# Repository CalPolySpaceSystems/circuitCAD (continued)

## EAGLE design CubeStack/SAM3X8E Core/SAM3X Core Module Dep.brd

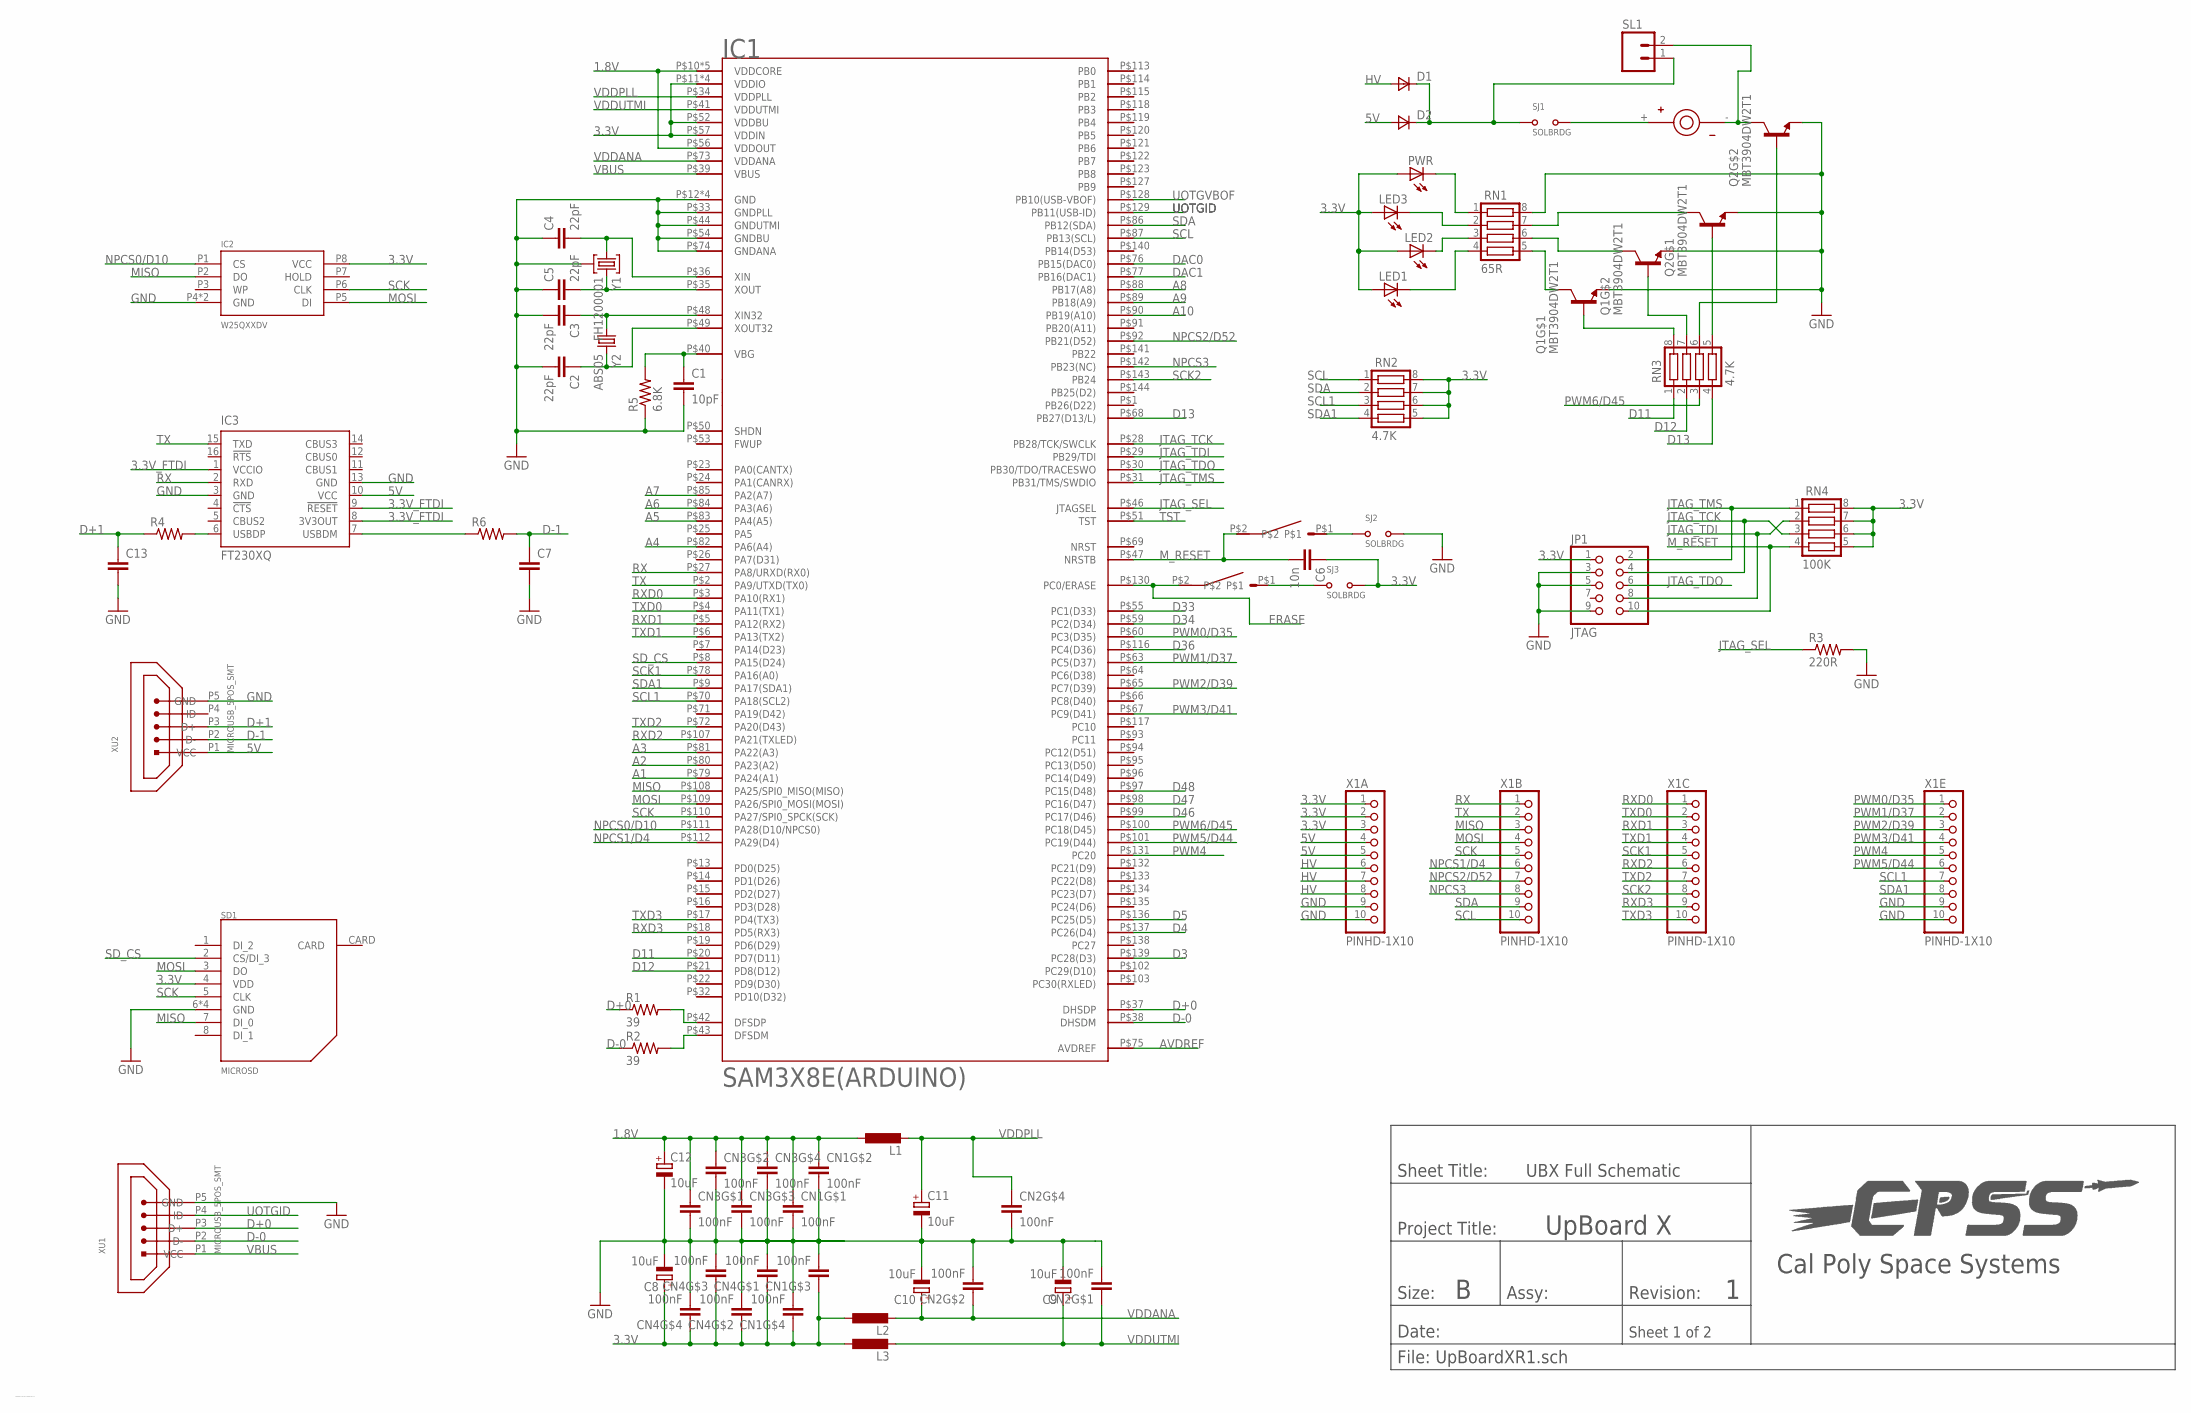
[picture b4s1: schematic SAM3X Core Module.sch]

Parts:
C1: 10pF; C0603
C2, C3, C4, C5: 22pF; C0603
C6: 10n; C0603
C7, C13: C-EUC0603; C0603
C8, C9, C10, C11, C12: 10uF; A/3216-18R
CN1, CN2, CN3, CN4: 100nF; 1206-4
D1, D2: DSOD323; SOD323
ERASE: 1000P; B3U-1000P
IC1: SAM3X8E(ARDUINO); 144-LEAD_LQFP
IC2: W25QXXDV; WSON
IC3: FT230XQ; QFN16
JP1: JTAG; 2X5-PTH-1.27MM
L1, L2, L3: L-EU0402; C0402
LED1, LED2, LED3: LEDCHIPLED_0805; CHIPLED_0805
LS1: AI-1440-TWT-24V-2-R; AI-1440-TWT-24-2-R
PWR: LEDCHIPLED_0805; CHIPLED_0805
Q1, Q2: MBT3904DW2T1; SOT-363
R1, R2: 39; R0603
R3: 220R; R0402
R4, R6: R-US_R0603; R0603
R5: 6.8K; R0603
RESET: 1000P; B3U-1000P
RN1: 65R; CTS742C083
RN2, RN3: 4.7K; CTS742C083
RN4: 100K; CTS742C083
SD1: MICROSD; CONN_MICROSD
SJ1, SJ2, SJ3: SOLBRDG
SL1: M02; 02P
X1A, X1B, X1C, X1E: PINHD-1X10; 1X10-BIG
XU1, XU2: MICROUSB_5POS_SMT; RECPT_SMT_R/A
Y1: FH1200001; MINISMD
Y2: ABS05; FC-12M

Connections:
1.8V: C12.+, CN1.P$1 (1), CN1.P$2 (1), CN3.P$1 (1), CN3.P$2 (1), CN3.P$3 (1), CN3.P$4 (1), IC1.P$10 (VDDCORE), IC1.P$45 (VDDCORE), IC1.P$56 (VDDOUT), IC1.P$61 (VDDCORE), IC1.P$104 (VDDCORE), IC1.P$124 (VDDCORE), L1.1
3.3V: C6.1, C8.+, CN1.P$3 (1), CN1.P$4 (1), CN4.P$1 (1), CN4.P$2 (1), CN4.P$3 (1), CN4.P$4 (1), IC1.P$11 (VDDIO), IC1.P$52 (VDDBU), IC1.P$57 (VDDIN), IC1.P$62 (VDDIO), IC1.P$105 (VDDIO), IC1.P$125 (VDDIO), IC2.P8 (VCC), JP1.1, L2.1, L3.1, LED1.A, LED2.A, LED3.A, PWR.A, RN2.5, RN2.6, RN2.7, RN2.8, RN4.5, RN4.6, RN4.7, RN4.8, SD1.4 (VDD), SJ3.P$2, X1A.1, X1A.2, X1A.3; also elsewhere on the board
3.3V_FTDI: IC3.1 (VCCIO), IC3.8 (3V3OUT), IC3.9 (!RESET)
5V: D2.2 (A), IC3.10 (VCC), X1A.4, X1A.5, XU2.P1 (VCC)
A1: IC1.P$79 (PA24(A1))
A2: IC1.P$80 (PA23(A2))
A3: IC1.P$81 (PA22(A3))
A4: IC1.P$82 (PA6(A4))
A5: IC1.P$83 (PA4(A5))
A6: IC1.P$84 (PA3(A6))
A7: IC1.P$85 (PA2(A7))
A8: IC1.P$88 (PB17(A8))
A9: IC1.P$89 (PB18(A9))
A10: IC1.P$90 (PB19(A10))
AVDREF: IC1.P$75 (AVDREF)
D3: IC1.P$139 (PC28(D3))
D4: IC1.P$137 (PC26(D4))
D5: IC1.P$136 (PC25(D5))
D11: IC1.P$20 (PD7(D11)), RN3.1
D12: IC1.P$21 (PD8(D12)), RN3.2
D13: IC1.P$68 (PB27(D13/L)), RN3.4
D33: IC1.P$55 (PC1(D33))
D34: IC1.P$59 (PC2(D34))
D36: IC1.P$116 (PC4(D36))
D46: IC1.P$99 (PC17(D46))
D47: IC1.P$98 (PC16(D47))
D48: IC1.P$97 (PC15(D48))
D+0: IC1.P$37 (DHSDP), R1.1, XU1.P3 (D+)
D+1: C13.1, R4.1, XU2.P3 (D+)
D-0: IC1.P$38 (DHSDM), R2.1, XU1.P2 (D-)
D-1: C7.1, R6.2, XU2.P2 (D-)
DAC0: IC1.P$76 (PB15(DAC0))
DAC1: IC1.P$77 (PB16(DAC1))
ERASE: ERASE.P$2, IC1.P$130 (PC0/ERASE)
GND: C1.2, C2.2, C3.2, C4.1, C5.1, C7.2, C8.-, C9.-, C10.-, C11.-, C12.-, C13.2, CN1.P$5 (2), CN1.P$6 (2), CN1.P$7 (2), CN1.P$8 (2), CN2.P$5 (2), CN2.P$6 (2), CN2.P$8 (2), CN3.P$5 (2), CN3.P$6 (2), CN3.P$7 (2), CN3.P$8 (2), CN4.P$5 (2), CN4.P$6 (2), CN4.P$7 (2), CN4.P$8 (2), IC1.P$12 (GND), IC1.P$33 (GNDPLL), IC1.P$44 (GNDUTMI), IC1.P$54 (GNDBU), IC1.P$58 (GND), IC1.P$74 (GNDANA), IC1.P$106 (GND), IC1.P$126 (GND), IC2.P4 (GND), IC2.TH (GND), IC3.3 (GND), IC3.13 (GND), JP1.3, JP1.5, JP1.9, Q1.P$1 (E), Q1.P$4 (E), Q2.P$1 (E), Q2.P$4 (E), R3.2, R5.1, RN1.8, SD1.6 (GND), SD1.GND1 (GND), SD1.GND2 (GND), SD1.GND3 (GND), SJ2.P$2, X1A.9, X1A.10, X1E.9, X1E.10, XU1.P5 (GND), XU2.P5 (GND), Y1.GND2 (2), Y1.GND4 (2); also elsewhere on the board
HV: D1.2 (A), X1A.6, X1A.7, X1A.8
JTAG_SEL: IC1.P$46 (JTAGSEL), R3.1
JTAG_TCK: IC1.P$28 (PB28/TCK/SWCLK), JP1.4, RN4.3
JTAG_TDI: IC1.P$29 (PB29/TDI), JP1.8, RN4.2
JTAG_TDO: IC1.P$30 (PB30/TDO/TRACESWO), JP1.6
JTAG_TMS: IC1.P$31 (PB31/TMS/SWDIO), JP1.2, RN4.1
LS_D: LS1.-, Q2.P$6 (C), SL1.2
LS_DRIVE: D1.1 (C), D2.1 (C), SJ1.P$1, SL1.1
LS_G: Q2.P$2 (B), RN3.6
L_1: LED1.C, RN1.4
L_1_D: Q1.P$3 (C), RN1.5
L_1_G: Q1.P$5 (B), RN3.8
L_2: LED2.C, RN1.3
L_2_D: Q1.P$6 (C), RN1.6
L_2_G: Q1.P$2 (B), RN3.7
L_3: LED3.C, RN1.2
L_3_D: Q2.P$3 (C), RN1.7
L_3_G: Q2.P$5 (B), RN3.5
L_PWR_D: PWR.C, RN1.1
MISO: IC1.P$108 (PA25/SPI0_MISO(MISO)), IC2.P2 (DO), SD1.7 (DI_0), X1B.3
MOSI: IC1.P$109 (PA26/SPI0_MOSI(MOSI)), IC2.P5 (DI), SD1.3 (DO), X1B.4
M_RESET: C6.2, IC1.P$47 (NRSTB), JP1.10, RESET.P$2, RN4.4
unnamed: LS1.+, SJ1.P$2
unnamed: IC1.P$42 (DFSDP), R1.2
unnamed: IC3.6 (USBDP), R4.2
unnamed: IC3.7 (USBDM), R6.1
unnamed: RESET.P$1, SJ2.P$1
unnamed: IC1.P$43 (DFSDM), R2.2
unnamed: ERASE.P$1, SJ3.P$1
unnamed: C2.1, IC1.P$49 (XOUT32), Y2.2
unnamed: C3.1, IC1.P$48 (XIN32), Y2.1
unnamed: C1.1, IC1.P$40 (VBG), R5.2
NPCS0/D10: IC1.P$111 (PA28(D10/NPCS0)), IC2.P1 (CS); also elsewhere on the board
NPCS1/D4: IC1.P$112 (PA29(D4)), X1B.6
NPCS2/D52: IC1.P$92 (PB21(D52)), X1B.7
NPCS3: IC1.P$142 (PB23(NC)), X1B.8
PWM0/D35: IC1.P$60 (PC3(D35)), X1E.1
PWM1/D37: IC1.P$63 (PC5(D37)), X1E.2
PWM2/D39: IC1.P$65 (PC7(D39)), X1E.3
PWM3/D41: IC1.P$67 (PC9(D41)), X1E.4
PWM4: IC1.P$131 (PC20), X1E.5
PWM5/D44: IC1.P$101 (PC19(D44)), X1E.6
PWM6/D45: IC1.P$100 (PC18(D45)), RN3.3
RX: IC1.P$27 (PA8/URXD(RX0)), IC3.2 (RXD), X1B.1
RXD0: IC1.P$3 (PA10(RX1)), X1C.1
RXD1: IC1.P$5 (PA12(RX2)), X1C.3
RXD2: IC1.P$107 (PA21(TXLED)), X1C.6
RXD3: IC1.P$18 (PD5(RX3)), X1C.9
SCK: IC1.P$110 (PA27/SPI0_SPCK(SCK)), IC2.P6 (CLK), SD1.5 (CLK), X1B.5
SCK1: IC1.P$78 (PA16(A0)), X1C.5
SCK2: IC1.P$143 (PB24), X1C.8
SCL: IC1.P$87 (PB13(SCL)), RN2.1, X1B.10
SCL1: IC1.P$70 (PA18(SCL2)), RN2.3, X1E.7
SDA: IC1.P$86 (PB12(SDA)), RN2.2, X1B.9
SDA1: IC1.P$9 (PA17(SDA1)), RN2.4, X1E.8
SD_CS: IC1.P$8 (PA15(D24)), SD1.2 (CS/DI_3)
TST: IC1.P$51 (TST)
TX: IC1.P$2 (PA9/UTXD(TX0)), IC3.15 (TXD), X1B.2
TXD0: IC1.P$4 (PA11(TX1)), X1C.2
TXD1: IC1.P$6 (PA13(TX2)), X1C.4
TXD2: IC1.P$72 (PA20(D43)), X1C.7
TXD3: IC1.P$17 (PD4(TX3)), X1C.10
UOTGID: IC1.P$129 (PB11(USB-ID)), XU1.P4 (ID)
UOTGVBOF: IC1.P$128 (PB10(USB-VBOF))
VBUS: IC1.P$39 (VBUS), XU1.P1 (VCC)
VDDANA: C10.+, CN2.P$2 (1), IC1.P$73 (VDDANA), L2.2
VDDPLL: C11.+, CN2.P$4 (1), IC1.P$34 (VDDPLL), L1.2
VDDUTMI: C9.+, CN2.P$1 (1), IC1.P$41 (VDDUTMI), L3.2
XCK_N: C5.2, IC1.P$35 (XOUT), Y1.P3 (3)
XCK_P: C4.2, IC1.P$36 (XIN), Y1.P1 (1)

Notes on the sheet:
Assy:
Size:
Revision:
Sheet 1 of 2
Date:
Sheet Title:
Project Title:
File: UpBoardXR1.sch
UBX Full Schematic
UpBoard X
C:/Users/Patrick Chizek/Pictures/CPSSLOGO.bmp
Cal Poly Space Systems

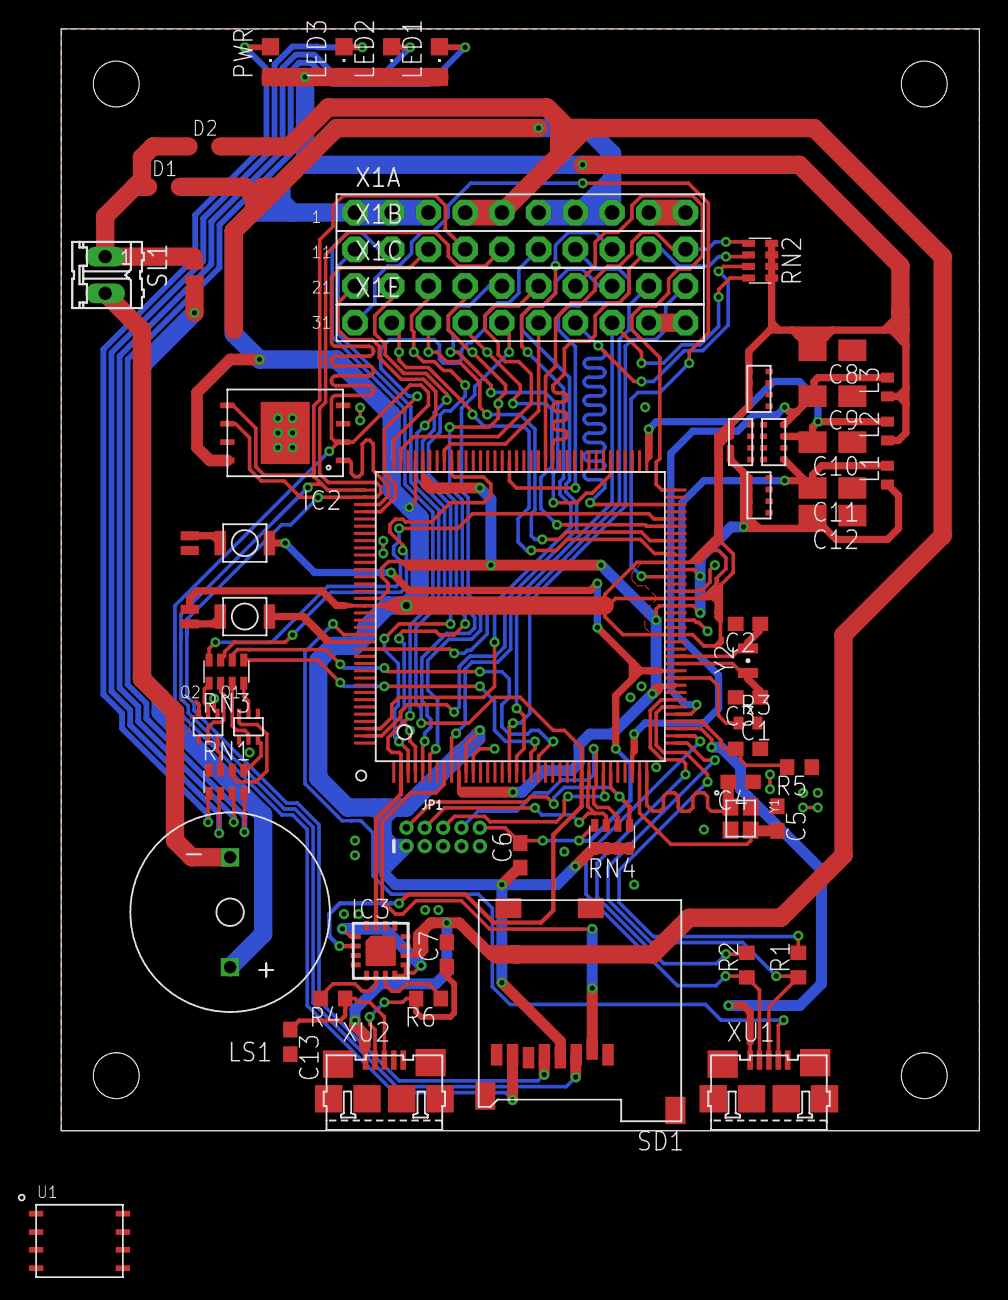
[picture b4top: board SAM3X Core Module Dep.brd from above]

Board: 2 copper layers, 63.5 x 76.2 mm, 59 parts (0 on the bottom side), 81 nets.

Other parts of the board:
U1: SST26VF064B; SOIJ

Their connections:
3.3V: U1.P$8; also elsewhere on the board
GND: U1.P$4; also elsewhere on the board
NPCS0/D10: U1.P$1; also elsewhere on the board

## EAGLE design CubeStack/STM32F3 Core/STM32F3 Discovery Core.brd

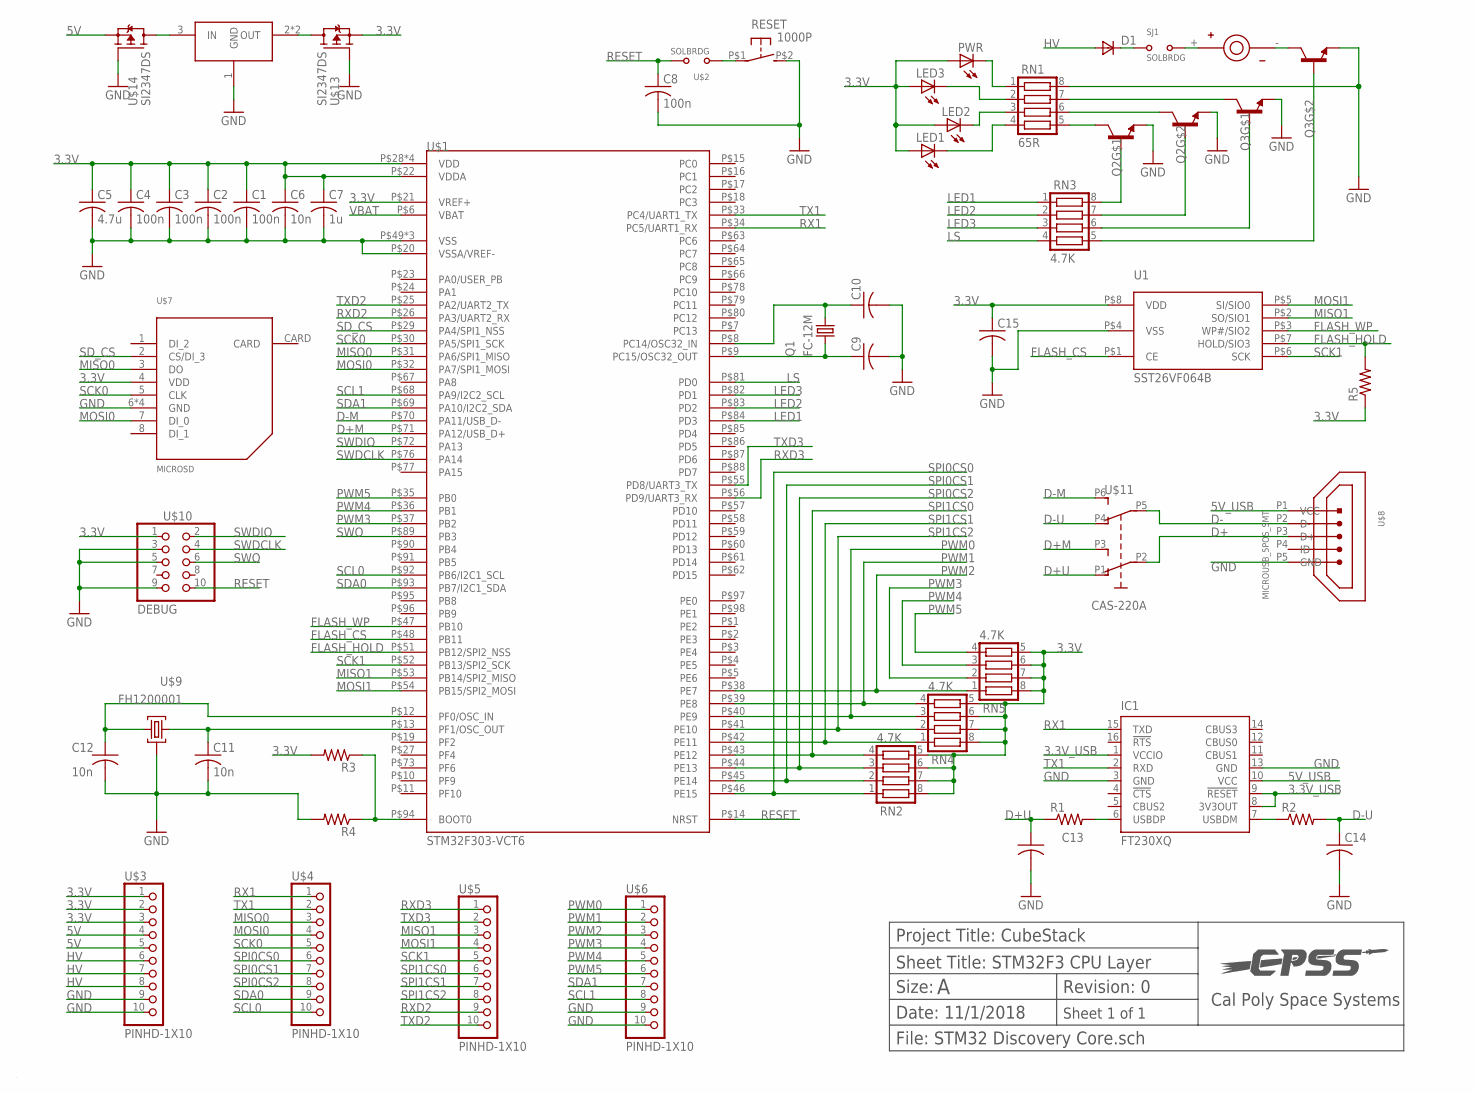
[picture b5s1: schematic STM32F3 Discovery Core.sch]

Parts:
C1, C2, C3, C4: 100n; C0805
C5: 4.7u; C0805
C6: 10n; C0805
C7: 1u; C0805
C8: 100n; C0603
C9, C10, C15: C-USC0402; C0402
C11, C12: 10n; C0402
C13, C14: C-USC0603; C0603
D1: DSOD323; SOD323
IC1: FT230XQ; QFN16
LED1, LED2, LED3: LEDCHIPLED_0805; CHIPLED_0805
LS1: AI-1440-TWT-24V-2-R; AI-1440-TWT-24-2-R
PWR: LEDCHIPLED_0805; CHIPLED_0805
Q1: FC-12M
Q2, Q3: MBT3904DW2T1; SOT-363
R1, R2, R3, R4, R5: R-US_R0603; R0603
RESET: 1000P; B3U-1000P
RN1: 65R; CTS742C083
RN2, RN3, RN4, RN5: 4.7K; CTS742C083
SJ1: SOLBRDG
U1: SST26VF064B; SOIJ
U$1: STM32F303-VCT6; LQFP-100
U$2: SOLBRDG
U$3, U$4, U$5, U$6: PINHD-1X10; 1X10-BIG
U$7: MICROSD; CONN_MICROSD
U$8: MICROUSB_5POS_SMT; RECPT_SMT_R/A
U$9: FH1200001; MINISMD
U$10: DEBUG; 2X5-PTH-1.27MM
U$11: CAS-220A; CAS220B1
U$12: AZ1117C; SOT89
U$13, U$14: SI2347DS; SOT23

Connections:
3.3V: C1.1, C2.1, C3.1, C4.1, C5.1, C6.1, C7.1, C15.1, LED1.A, LED2.A, LED3.A, PWR.A, R3.2, R5.1, RN2.5, RN2.6, RN2.7, RN2.8, RN4.5, RN4.6, RN4.7, RN4.8, RN5.5, RN5.6, RN5.7, RN5.8, U1.P$8 (VDD), U$1.P$21 (VREF+), U$1.P$22 (VDDA), U$1.P$28 (VDD), U$1.P$50 (VDD), U$1.P$75 (VDD), U$1.P$100 (VDD), U$3.1, U$3.2, U$3.3, U$7.4 (VDD), U$10.1, U$13.2 (S)
3.3V_USB: IC1.1 (VCCIO), IC1.8 (3V3OUT), IC1.9 (!RESET), U$12.2 (OUT), U$12.2@1 (OUT), U$13.3 (D)
5V: U$3.4, U$3.5, U$14.2 (S)
5V_USB: IC1.10 (VCC), U$8.P1 (VCC), U$12.3 (IN), U$14.3 (D)
D+: U$8.P3 (D+), U$11.P2
D+M: U$1.P$71 (PA12/USB_D+), U$11.P3 (S)
D+U: C13.1, R1.1, U$11.P1 (O)
D-: U$8.P2 (D-), U$11.P5 (P1)
D-M: U$1.P$70 (PA11/USB_D-), U$11.P6 (S1)
D-U: C14.1, R2.2, U$11.P4 (O1)
FLASH_CS: U1.P$1 (CE), U$1.P$48 (PB11)
FLASH_HOLD: R5.2, U1.P$7 (HOLD/SIO3), U$1.P$51 (PB12/SPI2_NSS)
FLASH_WP: U1.P$3 (WP#/SIO2), U$1.P$47 (PB10)
GND: C1.2, C2.2, C3.2, C4.2, C5.2, C6.2, C7.2, C8.2, C9.2, C10.2, C11.2, C12.2, C13.2, C14.2, C15.2, IC1.3 (GND), IC1.13 (GND), Q2.P$3 (E), Q2.P$6 (E), Q3.P$3 (E), Q3.P$6 (E), R4.2, RESET.P$2 (S), RN1.8, U1.P$4 (VSS), U$1.P$20 (VSSA/VREF-), U$1.P$49 (VSS), U$1.P$74 (VSS), U$1.P$99 (VSS), U$3.9, U$3.10, U$6.9, U$6.10, U$7.6 (GND), U$7.GND1 (GND), U$7.GND2 (GND), U$7.GND3 (GND), U$8.P5 (GND), U$9.GND2 (2), U$9.GND4 (2), U$10.3, U$10.5, U$10.9, U$12.1 (GND), U$13.1 (G), U$14.1 (G)
HV: D1.2 (A), U$3.6, U$3.7, U$3.8
LED1: RN3.1, U$1.P$84 (PD3)
LED2: RN3.2, U$1.P$83 (PD2)
LED3: RN3.3, U$1.P$82 (PD1)
LS: RN3.4, U$1.P$81 (PD0)
LS_D: LS1.-, Q3.P$5 (C)
LS_G: Q3.P$1 (B), RN3.5
L_1: LED1.C, RN1.4
L_1_D: Q2.P$4 (C), RN1.5
L_1_G: Q2.P$2 (B), RN3.8
L_2: LED2.C, RN1.3
L_2_D: Q2.P$5 (C), RN1.6
L_2_G: Q2.P$1 (B), RN3.7
L_3: LED3.C, RN1.2
L_3_D: Q3.P$4 (C), RN1.7
L_3_G: Q3.P$2 (B), RN3.6
L_PWR_D: PWR.C, RN1.1
MISO0: U$1.P$31 (PA6/SPI1_MISO), U$4.3, U$7.3 (DO)
MISO1: U1.P$2 (SO/SIO1), U$1.P$53 (PB14/SPI2_MISO), U$5.3
MOSI0: U$1.P$32 (PA7/SPI1_MOSI), U$4.4, U$7.7 (DI_0)
MOSI1: U1.P$5 (SI/SIO0), U$1.P$54 (PB15/SPI2_MOSI), U$5.4
unnamed: LS1.+, SJ1.P$2
unnamed: C10.1, Q1.2, U$1.P$8 (PC14/OSC32_IN)
unnamed: RESET.P$1, U$2.P$1
unnamed: C9.1, Q1.1, U$1.P$9 (PC15/OSC32_OUT)
unnamed: C12.1, U$1.P$12 (PF0/OSC_IN), U$9.P3 (3)
unnamed: C11.1, U$1.P$13 (PF1/OSC_OUT), U$9.P1 (1)
unnamed: D1.1 (C), SJ1.P$1
unnamed: IC1.6 (USBDP), R1.2
unnamed: IC1.7 (USBDM), R2.1
unnamed: R3.1, R4.1, U$1.P$94 (BOOT0)
PWM0: RN4.3, U$1.P$40 (PE9), U$6.1
PWM1: RN4.4, U$1.P$39 (PE8), U$6.2
PWM2: RN5.1, U$1.P$38 (PE7), U$6.3
PWM3: RN5.2, U$1.P$37 (PB2), U$6.4
PWM4: RN5.3, U$1.P$36 (PB1), U$6.5
PWM5: RN5.4, U$1.P$35 (PB0), U$6.6
RESET: C8.1, U$1.P$14 (NRST), U$2.P$2, U$10.10
RX1: IC1.15 (TXD), U$1.P$34 (PC5/UART1_RX), U$4.1
RXD2: U$1.P$26 (PA3/UART2_RX), U$5.9
RXD3: U$1.P$56 (PD9/UART3_RX), U$5.1
SCK0: U$1.P$30 (PA5/SPI1_SCK), U$4.5, U$7.5 (CLK)
SCK1: U1.P$6 (SCK), U$1.P$52 (PB13/SPI2_SCK), U$5.5
SCL0: U$1.P$92 (PB6/I2C1_SCL), U$4.10
SCL1: U$1.P$68 (PA9/I2C2_SCL), U$6.8
SDA0: U$1.P$93 (PB7/I2C1_SDA), U$4.9
SDA1: U$1.P$69 (PA10/I2C2_SDA), U$6.7
SD_CS: U$1.P$29 (PA4/SPI1_NSS), U$7.2 (CS/DI_3)
SPI0CS0: RN2.1, U$1.P$46 (PE15), U$4.6
SPI0CS1: RN2.2, U$1.P$45 (PE14), U$4.7
SPI0CS2: RN2.3, U$1.P$44 (PE13), U$4.8
SPI1CS0: RN2.4, U$1.P$43 (PE12), U$5.6
SPI1CS1: RN4.1, U$1.P$42 (PE11), U$5.7
SPI1CS2: RN4.2, U$1.P$41 (PE10), U$5.8
SWDCLK: U$1.P$76 (PA14), U$10.4
SWDIO: U$1.P$72 (PA13), U$10.2
SWO: U$1.P$89 (PB3), U$10.6
TX1: IC1.2 (RXD), U$1.P$33 (PC4/UART1_TX), U$4.2
TXD2: U$1.P$25 (PA2/UART2_TX), U$5.10
TXD3: U$1.P$55 (PD8/UART3_TX), U$5.2
VBAT: U$1.P$6 (VBAT)

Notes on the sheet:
Size:
Revision: 0
Sheet 1 of 1
Date: 11/1/2018
Sheet Title: STM32F3 CPU Layer
Project Title: CubeStack
File: STM32 Discovery Core.sch
Cal Poly Space Systems
C:/Users/patri/Pictures/CPSSLOGO.bmp

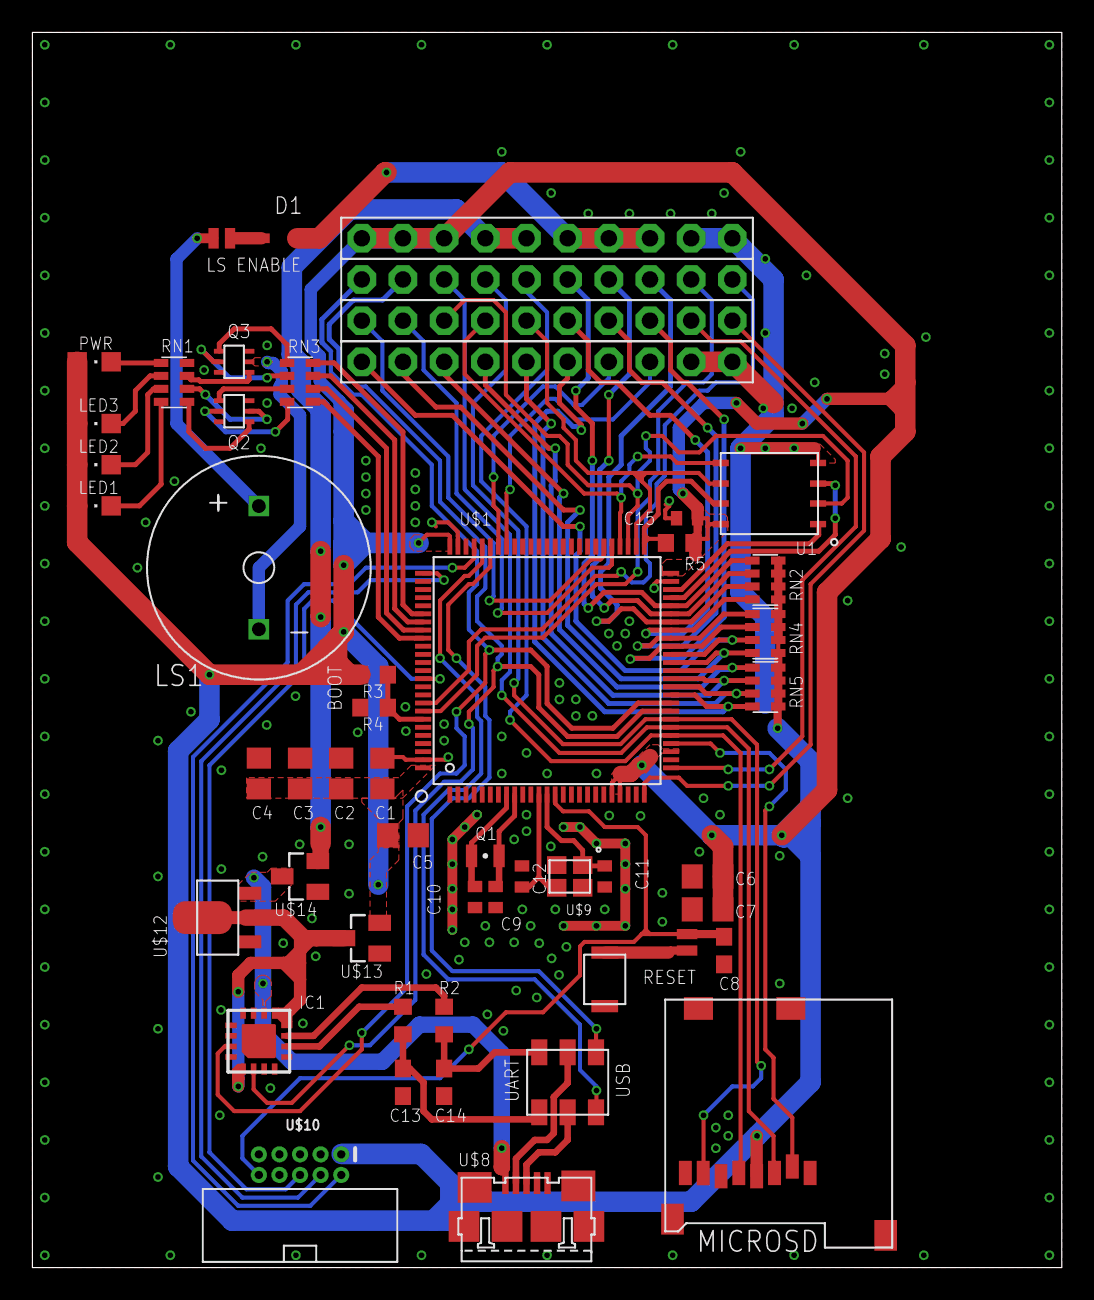
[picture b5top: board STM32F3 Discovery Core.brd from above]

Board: 2 copper layers, 63.5 x 76.2 mm, 52 parts (0 on the bottom side), 74 nets.

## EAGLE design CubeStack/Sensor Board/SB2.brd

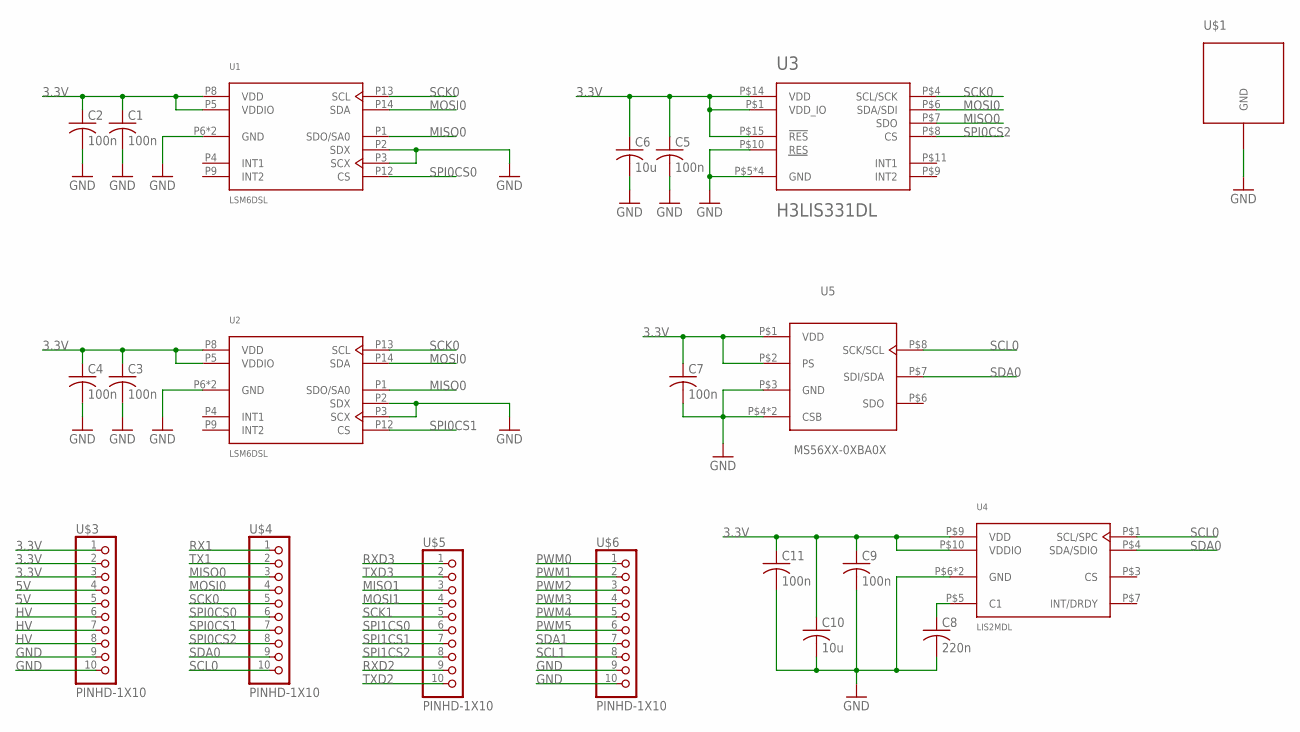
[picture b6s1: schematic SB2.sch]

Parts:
C1, C2, C3, C4, C5, C7, C9, C11: 100n; C0805
C6, C10: 10u; C0805
C8: 220n; C0805
U1, U2: LSM6DSL; LGA-14
U3: H3LIS331DL; TFLGA-16L
U4: LIS2MDL; LGA-12
U5: MS56XX-0XBA0X; MS56XX
U$1: EMI_SHIELD; BMI-S-210
U$3, U$4, U$5, U$6: PINHD-1X10; 1X10-BIG

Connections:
3.3V: C1.1, C2.1, C3.1, C4.1, C5.1, C6.1, C7.1, C9.1, C10.1, C11.1, U1.P5 (VDDIO), U1.P8 (VDD), U2.P5 (VDDIO), U2.P8 (VDD), U3.P$1 (VDD_IO), U3.P$14 (VDD), U3.P$15 (!RES), U4.P$9 (VDD), U4.P$10 (VDDIO), U5.P$1 (VDD), U5.P$2 (PS), U$3.1, U$3.2, U$3.3
5V: U$3.4, U$3.5
GND: C1.2, C2.2, C3.2, C4.2, C5.2, C6.2, C7.2, C8.2, C9.2, C10.2, C11.2, U1.P2 (SDX), U1.P3 (SCX), U1.P6 (GND), U1.P7 (GND), U2.P2 (SDX), U2.P3 (SCX), U2.P6 (GND), U2.P7 (GND), U3.P$5 (GND), U3.P$10 (RES), U3.P$12 (GND), U3.P$13 (GND), U3.P$16 (GND), U4.P$6 (GND), U4.P$8 (GND), U5.P$3 (GND), U5.P$4 (CSB), U5.P$5 (CSB), U$1.P$1, U$1.P$2, U$1.P$3, U$1.P$4, U$1.P$5, U$1.P$6, U$1.P$7, U$1.P$8, U$1.P$9, U$1.P$10, U$1.P$11, U$1.P$12, U$1.P$13, U$1.P$14, U$1.P$15, U$1.P$16, U$1.P$17, U$1.P$18, U$1.P$19, U$1.P$20, U$1.P$21, U$1.P$22, U$1.P$23, U$1.P$24, U$1.P$25, U$1.P$26, U$1.P$27, U$1.P$28, U$3.9, U$3.10, U$6.9, U$6.10
HV: U$3.6, U$3.7, U$3.8
MISO0: U1.P1 (SDO/SA0), U2.P1 (SDO/SA0), U3.P$7 (SDO), U$4.3
MISO1: U$5.3
MOSI0: U1.P14 (SDA), U2.P14 (SDA), U3.P$6 (SDA/SDI), U$4.4
MOSI1: U$5.4
unnamed: C8.1, U4.P$5 (C1)
PWM0: U$6.1
PWM1: U$6.2
PWM2: U$6.3
PWM3: U$6.4
PWM4: U$6.5
PWM5: U$6.6
RX1: U$4.1
RXD2: U$5.9
RXD3: U$5.1
SCK0: U1.P13 (SCL), U2.P13 (SCL), U3.P$4 (SCL/SCK), U$4.5
SCK1: U$5.5
SCL0: U4.P$1 (SCL/SPC), U5.P$8 (SCK/SCL), U$4.10
SCL1: U$6.8
SDA0: U4.P$4 (SDA/SDIO), U5.P$7 (SDI/SDA), U$4.9
SDA1: U$6.7
SPI0CS0: U1.P12 (CS), U$4.6
SPI0CS1: U2.P12 (CS), U$4.7
SPI0CS2: U3.P$8 (CS), U$4.8
SPI1CS0: U$5.6
SPI1CS1: U$5.7
SPI1CS2: U$5.8
TX1: U$4.2
TXD2: U$5.10
TXD3: U$5.2

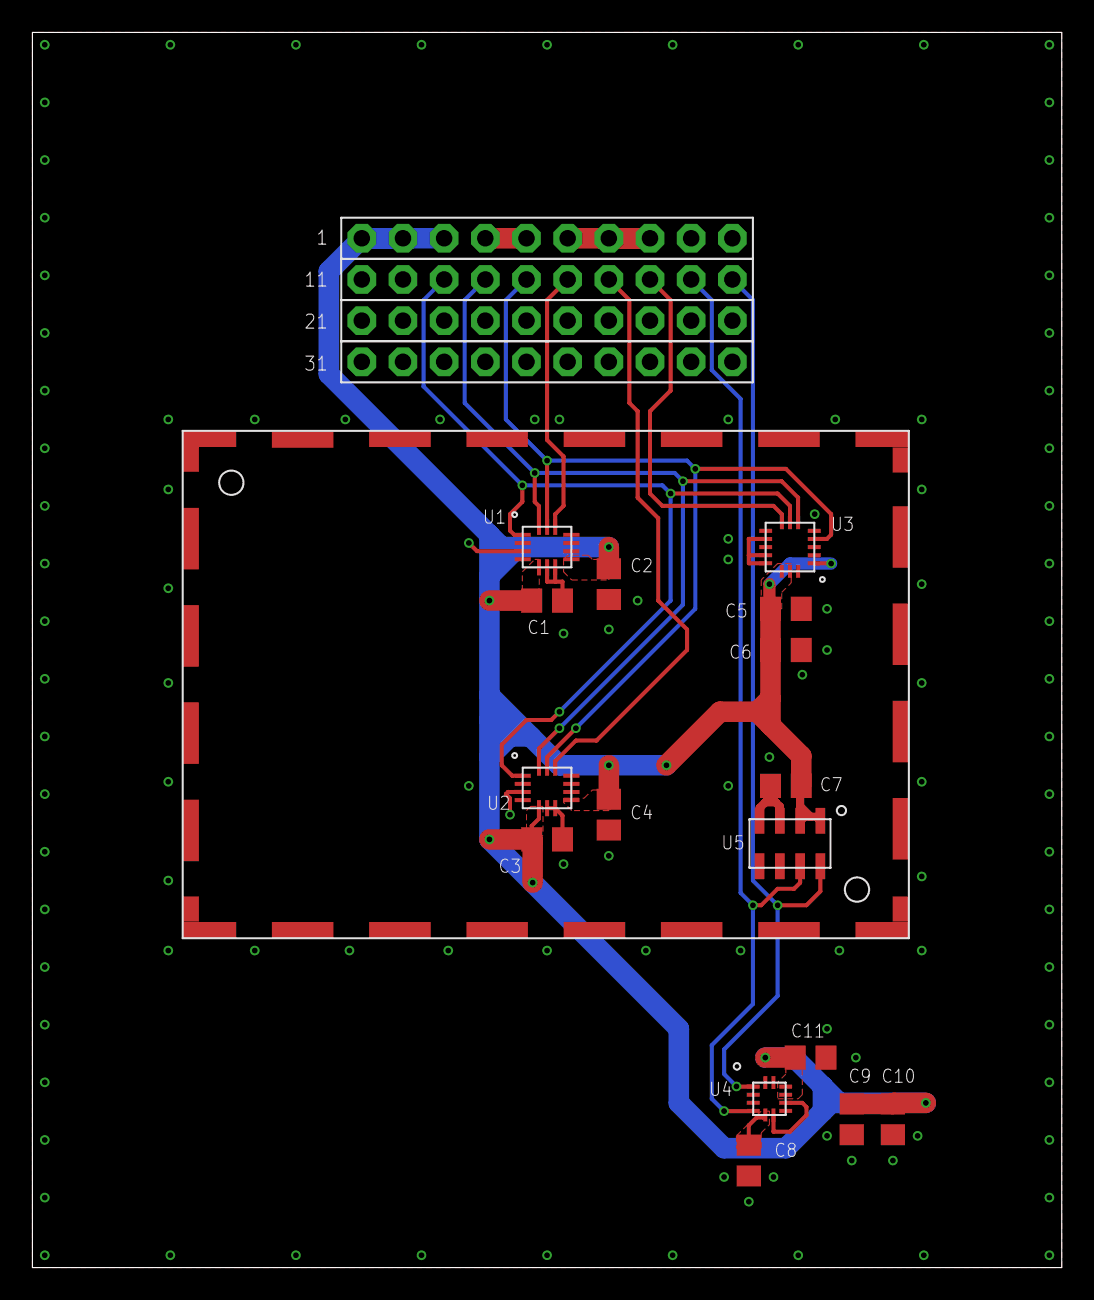
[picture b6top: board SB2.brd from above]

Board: 2 copper layers, 63.5 x 76.2 mm, 21 parts (0 on the bottom side), 13 nets.

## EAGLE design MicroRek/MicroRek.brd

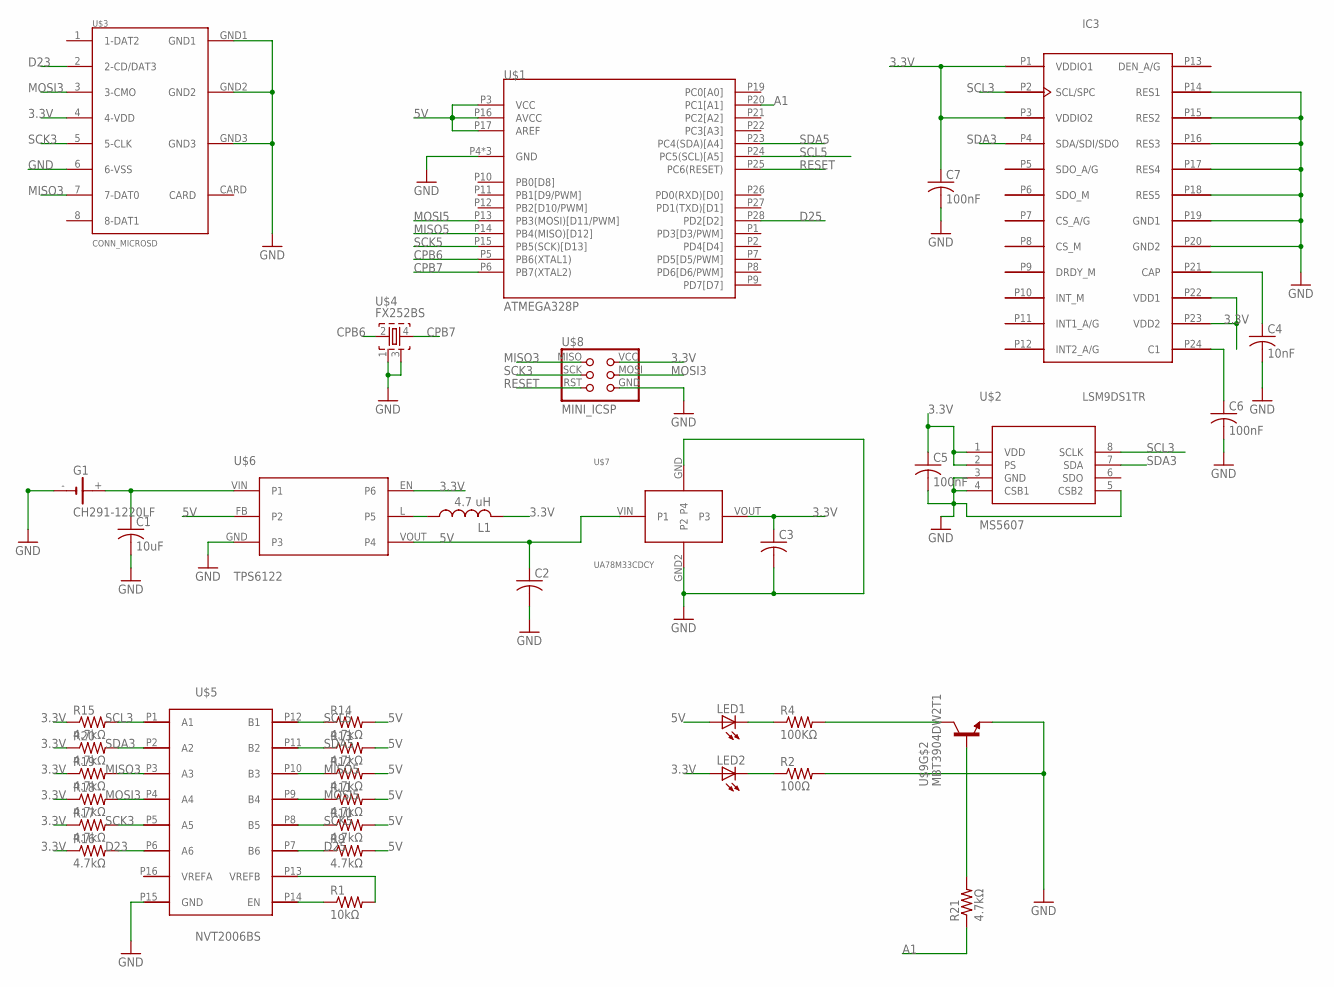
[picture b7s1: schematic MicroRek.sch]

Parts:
C1: 10uF; C0402
C2, C3: C-USC0402; C0402
C4: 10nF; C0402
C5, C6, C7: 100nF; C0402
G1: CH291-1220LF
IC3: LSM9DS1TR; LGA
L1: 4.7 uH; MICROREK_INDUCTOR
LED1, LED2: LEDCHIPLED_0805; CHIPLED_0805
R1: 10kΩ; R0603
R2: 100Ω; R0603
R4: 100KΩ; R0603
R9, R10, R11, R12, R13, R14, R15, R16, R17, R18, R19, R20, R21: 4.7kΩ; R0603
U$1: ATMEGA328P; VQFN-28
U$2: MS5607; 8-QFN
U$3: CONN_MICROSD
U$4: FX252BS; FA-20H
U$5: NVT2006BS; HVQFN16
U$6: TPS6122; TPS6122P
U$7: UA78M33CDCY; DCY
U$8: MINI_ICSP; NPNN032FFKS-RC
U$9: MBT3904DW2T1; SOT-363

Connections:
3.3V: C3.1, C5.1, C7.1, IC3.P1 (VDDIO1), IC3.P3 (VDDIO2), IC3.P22 (VDD1), IC3.P23 (VDD2), L1.P$2 (2), LED2.A, R15.1, R16.1, R17.1, R18.1, R19.1, R20.1, U$2.1 (VDD), U$2.2 (PS), U$3.4 (4-VDD), U$6.EN (P6), U$7.VOUT (P3), U$8.VCC (2)
5V: C2.1, LED1.A, R9.2, R10.2, R11.2, R12.2, R13.2, R14.2, U$1.P3 (VCC), U$1.P16 (AVCC), U$1.P17 (AREF), U$6.FB (P2), U$6.VOUT (P4), U$7.VIN (P1)
A1: R21.1, U$1.P20 (PC1[A1])
CPB6: U$1.P5 (PB6(XTAL1)), U$4.2 (1)
CPB7: U$1.P6 (PB7(XTAL2)), U$4.4 (3)
D23: R16.2, U$3.2 (2-CD/DAT3), U$5.P6 (A6)
D25: R9.1, U$1.P28 (PD2[D2]), U$5.P7 (B6)
GND: C1.2, C2.2, C3.2, C4.2, C5.2, C6.2, C7.2, G1.-, IC3.P14 (RES1), IC3.P15 (RES2), IC3.P16 (RES3), IC3.P17 (RES4), IC3.P18 (RES5), IC3.P19 (GND1), IC3.P20 (GND2), R2.2, U$1.P4 (GND), U$1.P18 (GND), U$1.TH (GND), U$2.3 (GND), U$2.4 (CSB1), U$2.5 (CSB2), U$3.6 (6-VSS), U$3.GND1, U$3.GND2, U$3.GND3, U$4.1 (2), U$4.3 (4), U$5.P15 (GND), U$6.GND (P3), U$7.GND (P4), U$7.GND2 (P2), U$8.GND (6), U$9.P$6 (E)
MISO3: R19.2, U$3.7 (7-DAT0), U$5.P3 (A3), U$8.MISO (1)
MISO5: R12.1, U$1.P14 (PB4(MISO)[D12]), U$5.P10 (B3)
MOSI3: R18.2, U$3.3 (3-CMO), U$5.P4 (A4), U$8.MOSI (4)
MOSI5: R11.1, U$1.P13 (PB3(MOSI)[D11/PWM]), U$5.P9 (B4)
unnamed: R1.1, U$5.P14 (EN)
unnamed: C1.1, G1.+, U$6.VIN (P1)
unnamed: L1.P$1 (1), U$6.L (P5)
unnamed: C4.1, IC3.P21 (CAP)
unnamed: C6.1, IC3.P24 (C1)
unnamed: LED1.C, R4.1
unnamed: R4.2, U$9.P$5 (C)
unnamed: LED2.C, R2.1
unnamed: R21.2, U$9.P$1 (B)
RESET: U$1.P25 (PC6(RESET)), U$8.RST (5)
SCK3: R17.2, U$3.5 (5-CLK), U$5.P5 (A5), U$8.SCK (3)
SCK5: R10.1, U$1.P15 (PB5(SCK)[D13]), U$5.P8 (B5)
SCL3: IC3.P2 (SCL/SPC), R15.2, U$2.8 (SCLK), U$5.P1 (A1)
SCL5: R14.1, U$1.P24 (PC5(SCL)[A5]), U$5.P12 (B1)
SDA3: IC3.P4 (SDA/SDI/SDO), R20.2, U$2.7 (SDA), U$5.P2 (A2)
SDA5: R13.1, U$1.P23 (PC4(SDA)[A4]), U$5.P11 (B2)
VREFB: R1.2, U$5.P13 (VREFB)

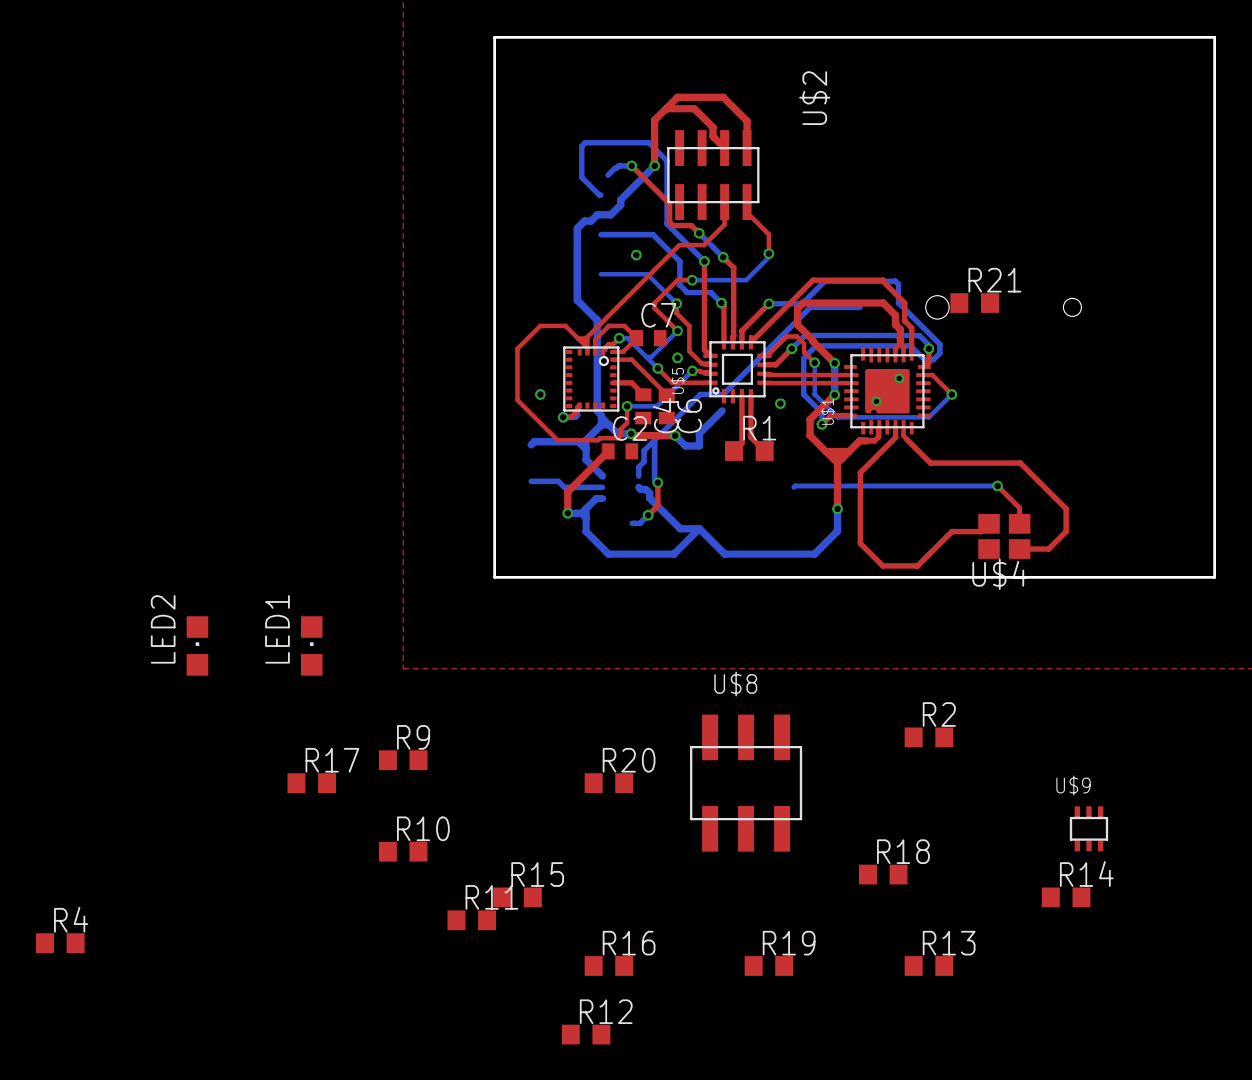
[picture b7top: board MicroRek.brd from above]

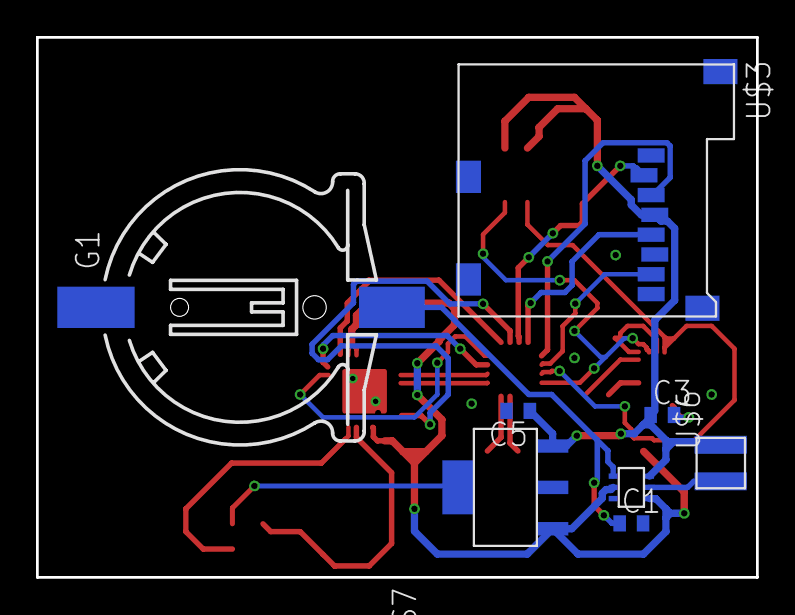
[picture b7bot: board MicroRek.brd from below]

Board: 2 copper layers, 40.0 x 30.0 mm, 37 parts (8 on the bottom side), 29 nets.
